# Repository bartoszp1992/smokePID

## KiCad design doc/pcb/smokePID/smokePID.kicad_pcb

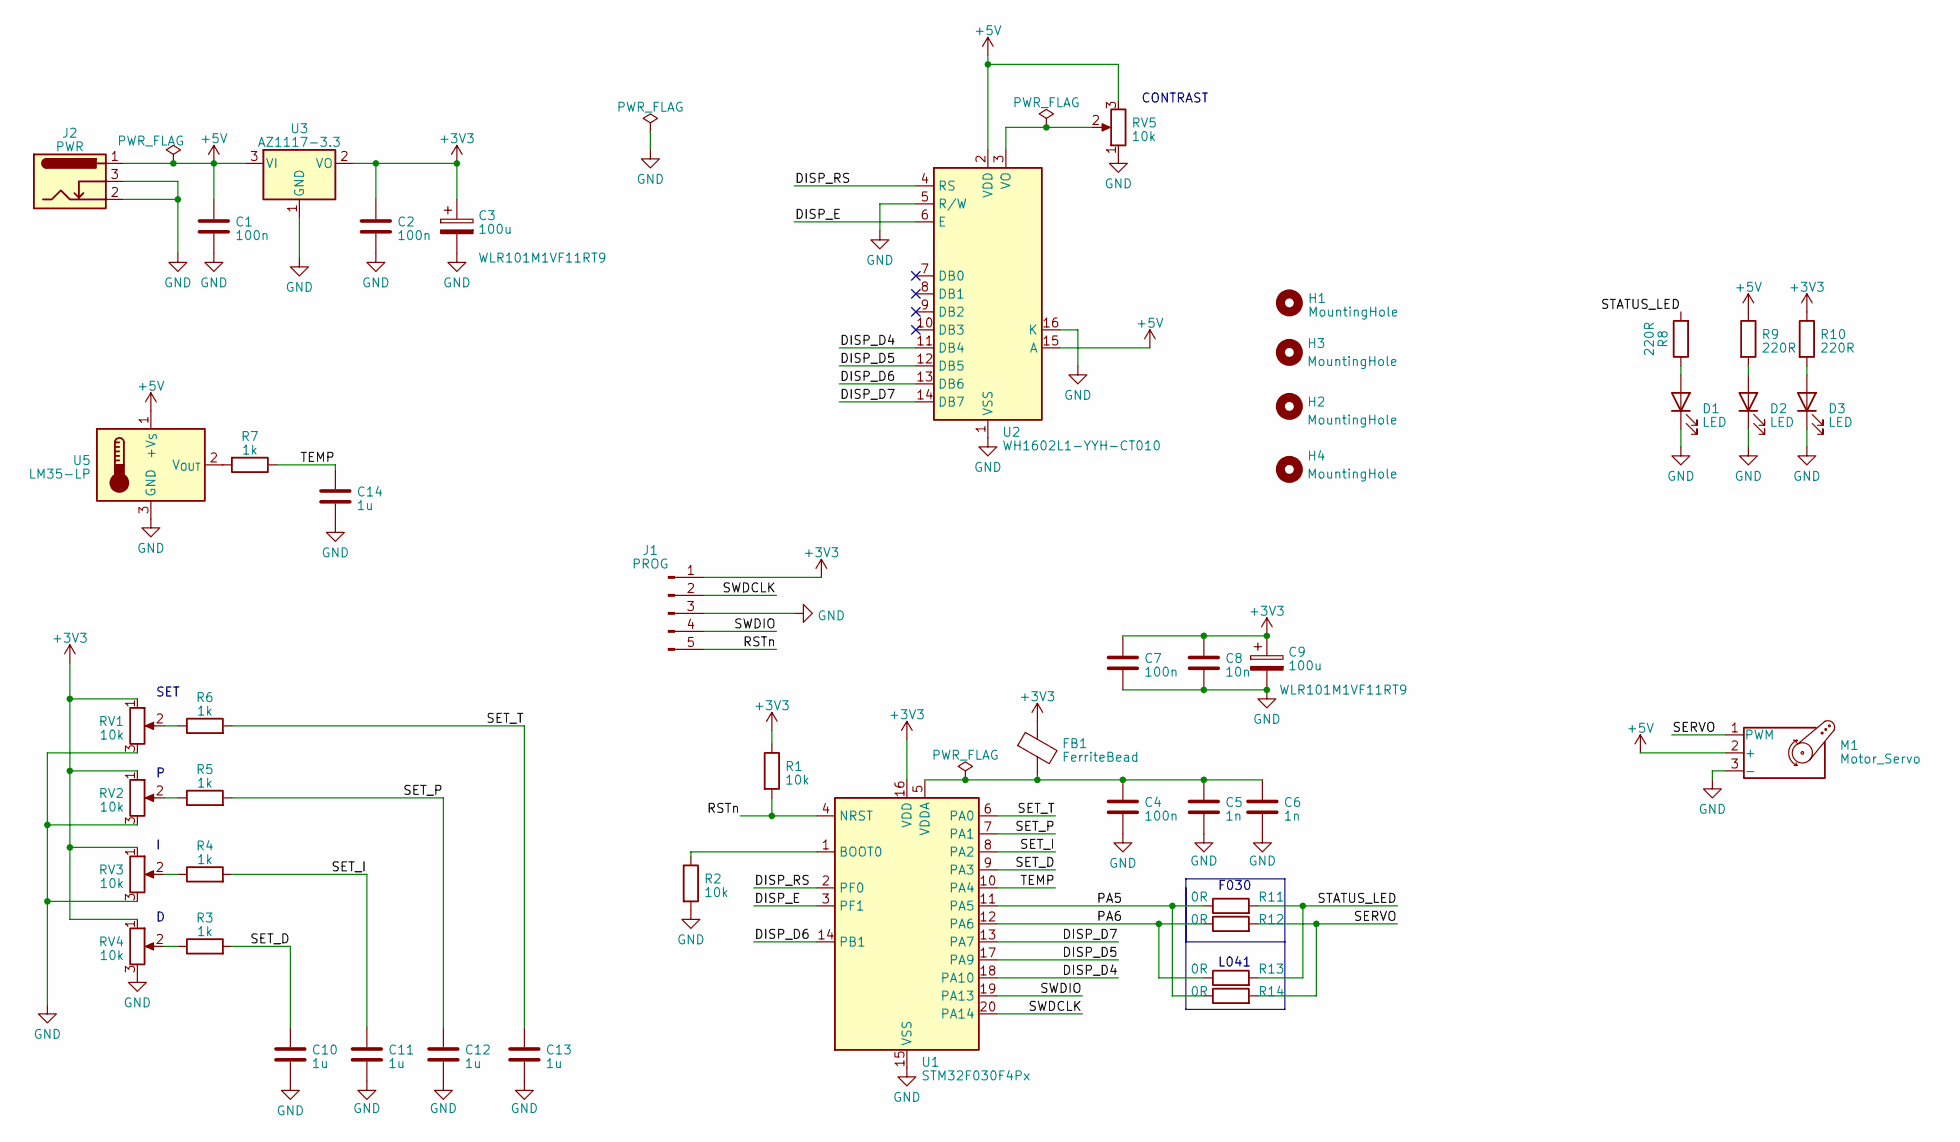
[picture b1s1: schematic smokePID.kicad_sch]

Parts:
C1, C2, C4, C7: 100n; C_0603_1608Metric
C3, C9: 100u; CP_Radial_D8.0mm_P3.50mm
C5, C6: 1n; C_0603_1608Metric
C8: 10n; C_0603_1608Metric
C10, C11, C12, C13, C14: 1u; C_0603_1608Metric
D1, D2, D3: LED; LED_0603_1608Metric
FB1: FerriteBead; L_0603_1608Metric
H1, H2, H3, H4: MountingHole; MountingHole_3.2mm_M3
J1: PROG; PinHeader_1x05_P2.54mm_Vertical
J2: PWR; BarrelJack_Horizontal
M1: Motor_Servo; PinHeader_1x03_P2.54mm_Vertical
R1, R2: 10k; R_0603_1608Metric
R3, R4, R5, R6, R7: 1k; R_0603_1608Metric
R8, R9, R10: 220R; R_0603_1608Metric
R11, R12, R13, R14: 0R; R_0603_1608Metric
RV1, RV2, RV3, RV4: 10k; Potentiometer_Alps_RK163_Single_Horizontal
RV5: 10k; Potentiometer_ACP_CA9-H5_Horizontal
U1: STM32F030F4Px; TSSOP-20_4.4x6.5mm_P0.65mm
U2: WH1602L1-YYH-CT010
U3: AZ1117-3.3; TO-252-2
U5: LM35-LP; PinHeader_1x03_P2.54mm_Vertical

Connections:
+3V3: C2.1, C3.1, C7.1, C8.1, C9.1, FB1.1, J1.1, R1.1, R10.1, RV1.1, RV2.1, RV3.1, RV4.1, U1.16 (VDD), U3.2 (VO)
+5V: C1.1, J2.1, M1.2 (+), R9.1, RV5.3, U2.2 (VDD), U2.15 (A), U3.3 (VI), U5.1 (+V_{S})
/DISP_D4: U1.18 (PA10), U2.11 (DB4)
/DISP_D5: U1.17 (PA9), U2.12 (DB5)
/DISP_D6: U1.14 (PB1), U2.13 (DB6)
/DISP_D7: U1.13 (PA7), U2.14 (DB7)
/DISP_E: U1.3 (PF1), U2.6 (E)
/DISP_RS: U1.2 (PF0), U2.4 (RS)
/PA5: R11.1, R14.1, U1.11 (PA5)
/PA6: R12.1, R13.1, U1.12 (PA6)
/RSTn: J1.5, R1.2, U1.4 (NRST)
/SERVO: M1.1 (PWM), R12.2, R14.2
/SET_D: C10.1, R3.2, U1.9 (PA3)
/SET_I: C11.1, R4.2, U1.8 (PA2)
/SET_P: C12.1, R5.2, U1.7 (PA1)
/SET_T: C13.1, R6.2, U1.6 (PA0)
/STATUS_LED: R8.2, R11.2, R13.2
/SWDCLK: J1.2, U1.20 (PA14)
/SWDIO: J1.4, U1.19 (PA13)
/TEMP: C14.1, R7.1, U1.10 (PA4)
GND: C1.2, C2.2, C3.2, C4.2, C5.2, C6.2, C7.2, C8.2, C9.2, C10.2, C11.2, C12.2, C13.2, C14.2, D1.1 (K), D2.1 (K), D3.1 (K), J1.3, J2.2, J2.3, M1.3 (-), R2.2, RV1.3, RV2.3, RV3.3, RV4.3, RV5.1, U1.15 (VSS), U2.1 (VSS), U2.5 (R/W), U2.16 (K), U3.1 (GND), U5.3 (GND)
unnamed: D1.2 (A), R8.1
unnamed: D2.2 (A), R9.2
unnamed: D3.2 (A), R10.2
unnamed: R3.1, RV4.2
unnamed: R4.1, RV3.2
unnamed: R5.1, RV2.2
unnamed: R6.1, RV1.2
unnamed: R2.1, U1.1 (BOOT0)
unnamed: C4.1, C5.1, C6.1, FB1.2, U1.5 (VDDA)
unnamed: RV5.2, U2.3 (VO)
unnamed: R7.2, U5.2 (V_{OUT})

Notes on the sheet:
CONTRAST
L041
F030
SET

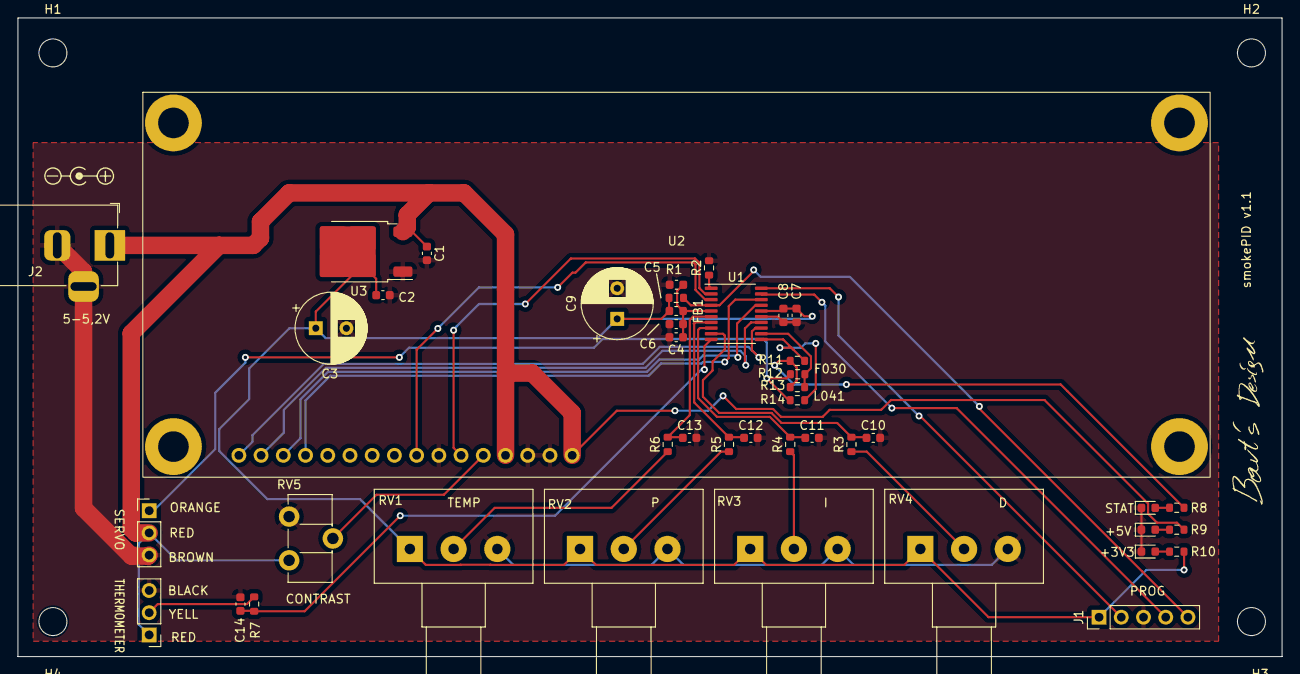
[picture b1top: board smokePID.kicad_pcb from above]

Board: 2 copper layers, 144.5 x 73.0 mm, 48 parts (0 on the bottom side), 32 nets.

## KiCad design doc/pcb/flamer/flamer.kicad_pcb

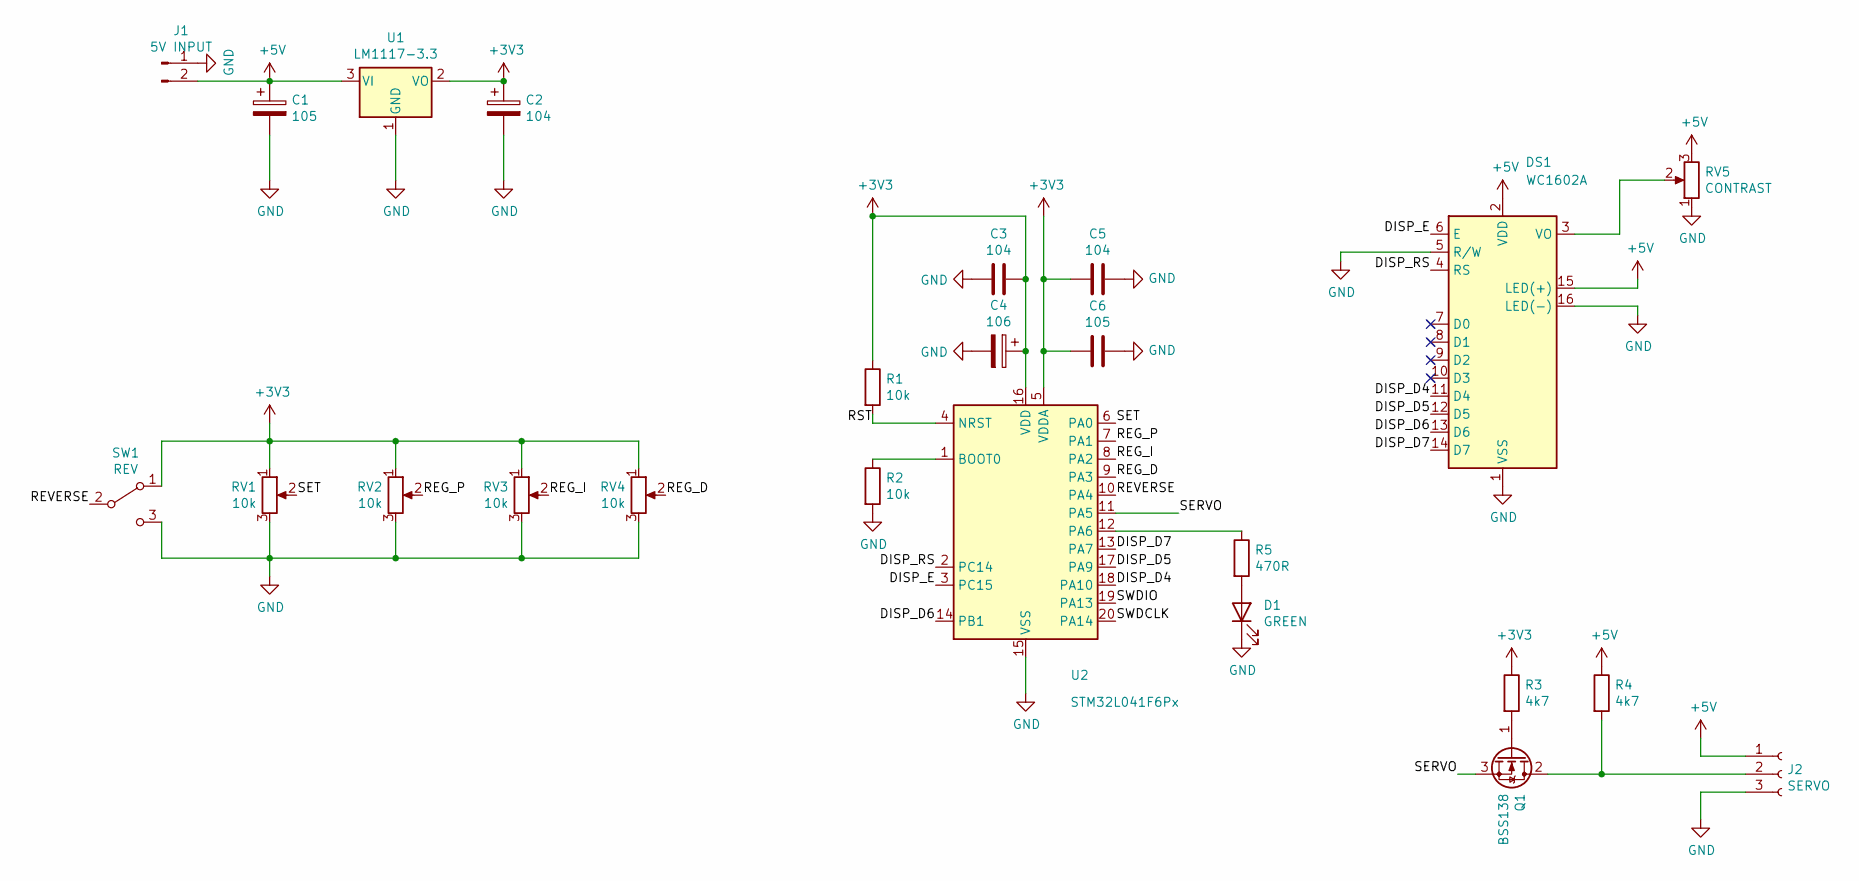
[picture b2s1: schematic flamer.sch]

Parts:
C1, C6: 105; C_0603_1608Metric
C2, C3, C5: 104; C_0603_1608Metric
C4: 106; CP_Radial_D5.0mm_P2.50mm
D1: GREEN; LED_0603_1608Metric
DS1: WC1602A
J1: 5V INPUT; AMASS_XT30UPB-F_1x02_P5.0mm_Vertical
J2: SERVO; PinHeader_1x03_P2.54mm_Vertical
Q1: BSS138; SOT-23
R1, R2: 10k; R_0603_1608Metric
R3, R4: 4k7; R_0603_1608Metric
R5: 470R; R_0603_1608Metric
RV1, RV2, RV3, RV4: 10k; Potentiometer_Alps_RK163_Single_Horizontal
RV5: CONTRAST; Potentiometer_ACP_CA9-H5_Horizontal
SW1: REV; PinSocket_1x03_P2.54mm_Vertical
U1: LM1117-3.3; TO-252-2
U2: STM32L041F6Px; TSSOP-20_4.4x6.5mm_P0.65mm

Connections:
+3V3: C2.1, C3.1, C4.1, C5.2, C6.1, R1.1, R3.1, RV1.1, RV2.1, RV3.1, RV4.1, SW1.1 (A), U1.2 (VO), U2.5 (VDDA), U2.16 (VDD)
+5V: C1.1, DS1.2 (VDD), DS1.15 (LED(+)), J1.2, J2.1, R4.1, RV5.3, U1.3 (VI)
/DISP_D4: DS1.11 (D4), U2.18 (PA10)
/DISP_D5: DS1.12 (D5), U2.17 (PA9)
/DISP_D6: DS1.13 (D6), U2.14 (PB1)
/DISP_D7: DS1.14 (D7), U2.13 (PA7)
/DISP_E: DS1.6 (E), U2.3 (PC15)
/DISP_RS: DS1.4 (RS), U2.2 (PC14)
/REG_D: RV4.2, U2.9 (PA3)
/REG_I: RV3.2, U2.8 (PA2)
/REG_P: RV2.2, U2.7 (PA1)
/REVERSE: SW1.2 (B), U2.10 (PA4)
/RST: R1.2, U2.4 (NRST)
/SERVO: Q1.3 (S), U2.11 (PA5)
/SET: RV1.2, U2.6 (PA0)
/SWDCLK: U2.20 (PA14)
/SWDIO: U2.19 (PA13)
GND: C1.2, C2.2, C3.2, C4.2, C5.1, C6.2, D1.1 (K), DS1.1 (VSS), DS1.5 (R/W), DS1.16 (LED(-)), J1.1, J2.3, R2.2, RV1.3, RV2.3, RV3.3, RV4.3, RV5.1, SW1.3 (C), U1.1 (GND), U2.15 (VSS)
unnamed: D1.2 (A), R5.2
unnamed: DS1.3 (VO), RV5.2
unnamed: J2.2, Q1.2 (D), R4.2
unnamed: Q1.1 (G), R3.2
unnamed: R2.1, U2.1 (BOOT0)
unnamed: R5.1, U2.12 (PA6)

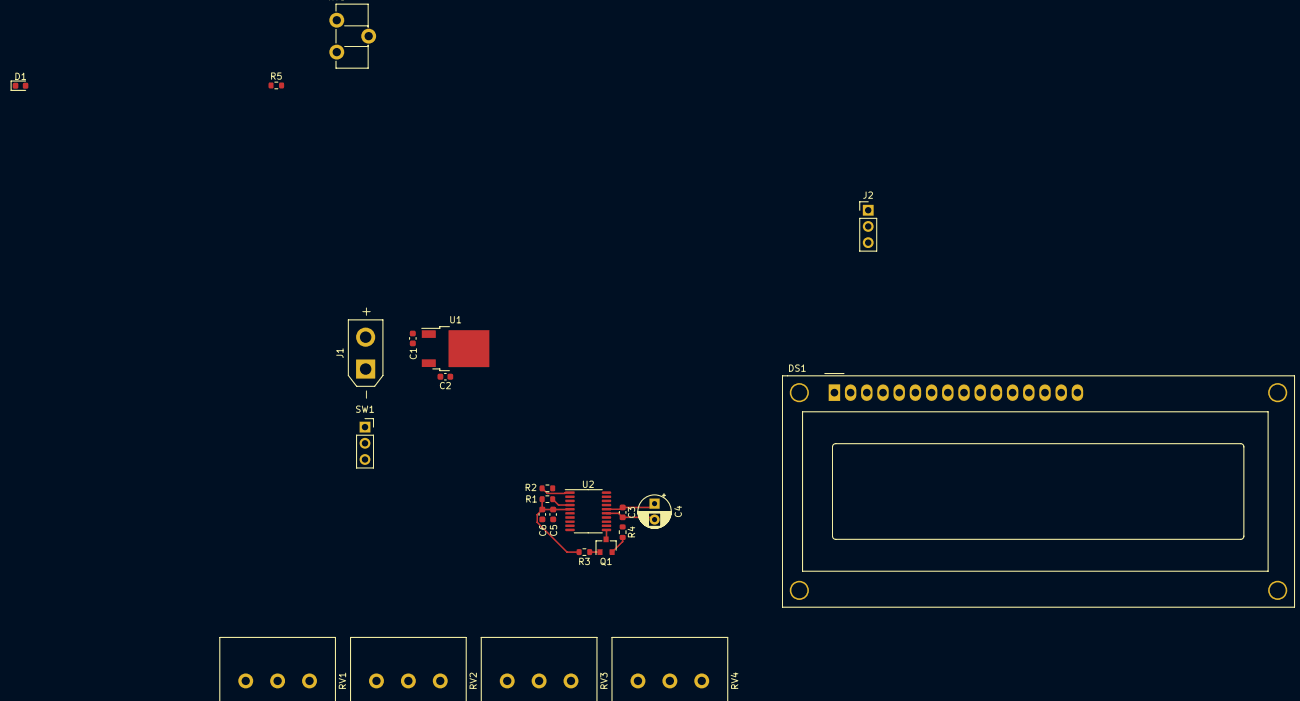
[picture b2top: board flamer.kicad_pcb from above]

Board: 2 copper layers, 24 parts (0 on the bottom side), 22 nets.

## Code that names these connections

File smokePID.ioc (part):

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Mcu.Name=STM32L041F6Px
Mcu.Package=TSSOP20
Mcu.UserName=STM32L041F6Px
PA0-CK_IN.GPIOParameters=GPIO_Label
PA0-CK_IN.GPIO_Label=SET
PA0-CK_IN.Mode=IN0
PA0-CK_IN.Signal=ADC_IN0
PA1.GPIOParameters=GPIO_Label
PA1.GPIO_Label=REG_P
PA1.Mode=IN1
PA1.Signal=ADC_IN1
PA10.GPIOParameters=GPIO_Label
PA10.GPIO_Label=DISP_D4
PA10.Signal=GPIO_Output
PA13.Mode=Serial_Wire
PA13.Signal=SYS_SWDIO
PA14.Mode=Serial_Wire
PA14.Signal=SYS_SWCLK
PA2.GPIOParameters=GPIO_Label
PA2.GPIO_Label=REG_I
PA2.Mode=IN2
PA2.Signal=ADC_IN2
PA3.GPIOParameters=GPIO_Label
PA3.GPIO_Label=REG_D
PA3.Mode=IN3
PA3.Signal=ADC_IN3
PA4.GPIOParameters=GPIO_Label
PA4.GPIO_Label=TEMP
PA4.Mode=IN4
PA4.Signal=ADC_IN4
PA5.GPIOParameters=GPIO_Label
PA5.GPIO_Label=SERVO
PA5.Signal=S_TIM2_CH1
PA6.GPIOParameters=GPIO_Label
PA6.GPIO_Label=LED_STATUS
PA6.Signal=GPIO_Output
PA7.GPIOParameters=GPIO_Label
PA7.GPIO_Label=DISP_D7
PA7.Signal=GPIO_Output
PA9.GPIOParameters=GPIO_Label
PA9.GPIO_Label=DISP_D5
PA9.Signal=GPIO_Output
PB1.GPIOParameters=GPIO_Label
PB1.GPIO_Label=DISP_D6
PB1.Signal=GPIO_Output
PC14-OSC32_IN.GPIOParameters=GPIO_Label
PC14-OSC32_IN.GPIO_Label=DISP_RS
PC14-OSC32_IN.Signal=GPIO_Output
PC15-OSC32_OUT.GPIOParameters=GPIO_Label
PC15-OSC32_OUT.GPIO_Label=DISP_E
PC15-OSC32_OUT.Signal=GPIO_Output
RCC.HSE_VALUE=8000000
RCC.SYSCLKFreq_VALUE=24000000
RCC.SYSCLKSource=RCC_SYSCLKSOURCE_PLLCLK
board=custom

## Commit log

2021-12-30 initial
2022-01-04 v1.1
2022-04-14 better derivetive
2023-06-16 new pcb
2023-07-01 fixed display
